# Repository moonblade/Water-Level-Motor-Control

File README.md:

# Water-Level-Motor-Control

A companion to water level indicator. Having a water level indicator is cool and all, dont get me wrong, but my lazy ass can't be bothered to get up and manually switch on the motor and switch it off when the indicator tells me to. So whats the solution? Of course, automate it.

The major issue preventing me from doing this along with the indicator was that the motor switch was an outdoor style, push on push off switch and it was a bit daunting to mess around with it and add my own relay circuits to it. So I had kept it aside for a while.

### Raspberry pi controller

In the meantime, I bought a raspberry pi, and wasn't really doing much on it, so thinking I should at least be using it for something, ended up setting up grafana, and prometheus on it to visualize the water levels in sweet graphs.

Then figured would mess around with it a tiny bit more, and ended up writing an overcomplicated piece of code that checks the measurements from the last 3 minutes from prometheus, averages it, and then displays that as the percentage. There was an intermittent issue that sometimes wrong readings would come up in the sensor on the motor, so wrote a filter that removes any reading that is greater than 2 standard deviations away from mean for the last 3 minutes, and then the average is taken. 

This worked well for a while, but prometheus was giving all sorts of errors. Couldn't be bothered to deal with them in the long run when changing timezone and the size gap were the solutions I had to content with, so scratched it all out and ended up just using a circular array to store the previous values and then doing the calculations on it instead. It works well. At presnt prometheus service is failing and need to debug why, but the graphs can wait for now

### Automatic controller

Figured I'd at least making some in roads on how to tackle this, so got a wemos d1 chip, and a four channel relay, and whipped up a quick prototype that could take instructions from firebase. Intentionally made it stupid and controlled by the rpi so that modifications can be made on the fly by changing rpi code without having to touch the chip. Anyway, it takes on or off command from the rtdb and if its internal state was different from the command given, it would turn on or off the motor as needed. There were some issues with me not understanding the wiring of the box, namely that the offswitch was a normally closed connection and the switch breaks the connection and not the other way around, so after a bit of headscratching ended up wiring that in series with the existing connection so that both the manual and the auto switch would work. Didn't want the hassle of a phone charger for power like last time, so wired up an ac to dc convertor within the circuit itself so that it could be powered with the current to motor itself.

connections

assembled into its box

Wiring into the switch

Final state

Added the corresponding code in raspberry pi code to turn it on and off when critical thresholds were reached and added a ui for user to control the settings and turn motor on and off manually and also to turn off automatic water control. Gave it a go and wonder of wonders, it worked.........for a day. 

Waking up the next day I see that it should have turned the motor on, but didnt'. It had broken the very next day, post mortem analysis showed that the relay rated for 10 A had pulled close to 15 A through it and thus had died on me. So chalked that upto a learning experience and figured the next version would need 30A relays.

### Auto controller v2

5V 30A relays are kinda hard to find, especially if you want them as multiple channel modules, you'd need to import them from US as they seem to be the only ones making it. So ordered a couple of relays, opted for single ones since the other ones would take too long, and started work on the next board.

Throughout this project I'd done pcb designs on eagle, and later [on easyEDA](https://easyeda.com/editor#id=b41bb882b032482bb2b21c925477a603) but whenever I try to get them printed (on normal paper as a test run), I'd find that it was too small, I dont know if its a library fault or the component I chose was wrong or some other printer settings. Even ignoring the pcb printing, when I tried to make holes on a copper clad to practice with a hand drill, the resulting "line" of holes was more like a curve and I'd have trouble fitting in anything close to an IC chip in it. So figured I still needed training before I could use custom pcbs, or better yet it would make sense to just print it commercially than go through this again.

Anyway for the second round, added a second ac to dc convertor so that I could determine the current state of the motor from external signals instead of relying on an internal toggle, this way I could turn off the motor even if it was turned on by hand. I had bought two relays figuring I could turn the two on switches with one and the off switch with the other, so when I got the board ready and wired it up that way, what ended up happening is that the motor could not be turned off. If you turn it off, it just turned back on again. Facepalm moment, thinking of connecting two different circuits in one relay.

Lesson learnt, ordered the next relay and waited for it. After it arrived, added that in and tested it. But it didn't seem to work properly, it worked in brief tests, ie it could turn off the motor when it was on, but nothing else. Wierd. So I took off the chip and tried to flash new code to it, only to realize the chip was not functioning anymore. So I ordered a couple of new chips and waited for it to arrive.

Meanwhile, the water level sensor up top decided it wanted to go for a swim and took a dive into the water tank killing itself. So ended up spending time creating a v2 for the sensor as well. Which was a whole another ordeal.

The fault implied a wrong connection somewhere in the board. Since this was already wired into the switch board, it was a pain in the ass to test each conenction. Finally figuring out that the board was fine, but I'd connected the two ac to dc convertors in reverse, the sensing one and the power one were interchanged. So connected it properly. And plugged in the new chips. The chips were working properly and doing their job but the raspberry pi code that I'd updated in the meantime was now broken, and the correct commands were not being sent to turn the motor on and off. Sigh. This is integration hell.

After two days of hard debugging, finally figured out the issue. It wasn't working ....wait for it..... because it was turned off in the settings. Sigh. Turned it on and it started working without a hitch.

new circuit

finished product in a shinier box

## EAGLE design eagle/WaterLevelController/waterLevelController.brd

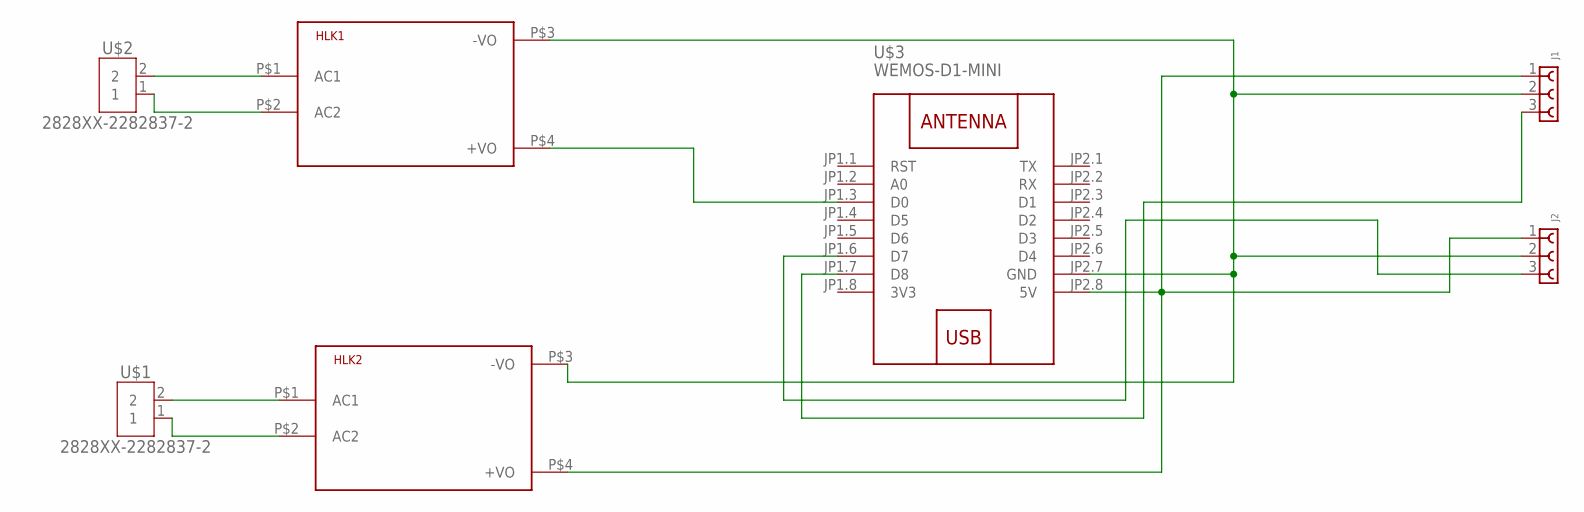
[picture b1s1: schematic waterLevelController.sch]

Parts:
HLK1, HLK2: HLK-PM013W; HLK-PM01
J1, J2: 6130XX11821_61300311821; 61300311821
U$1, U$2: 2828XX-2282837-2; TERMBLK_508-2N
U$3: WEMOS-D1-MINI

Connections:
3V3: U$3.JP1.8 (3V3)
unnamed: HLK1.P$2 (AC2), U$2.1
unnamed: HLK2.P$4 (+VO), J1.1, J2.1, U$3.JP2.8 (5V)
unnamed: HLK1.P$1 (AC1), U$2.2
unnamed: HLK1.P$3 (-VO), HLK2.P$3 (-VO), J1.2, J2.2, U$3.JP2.7 (GND)
unnamed: HLK2.P$2 (AC2), U$1.1
unnamed: HLK2.P$1 (AC1), U$1.2
unnamed: HLK1.P$4 (+VO), U$3.JP1.3 (D0)
unnamed: J1.3, U$3.JP1.7 (D8)
unnamed: J2.3, U$3.JP1.6 (D7)

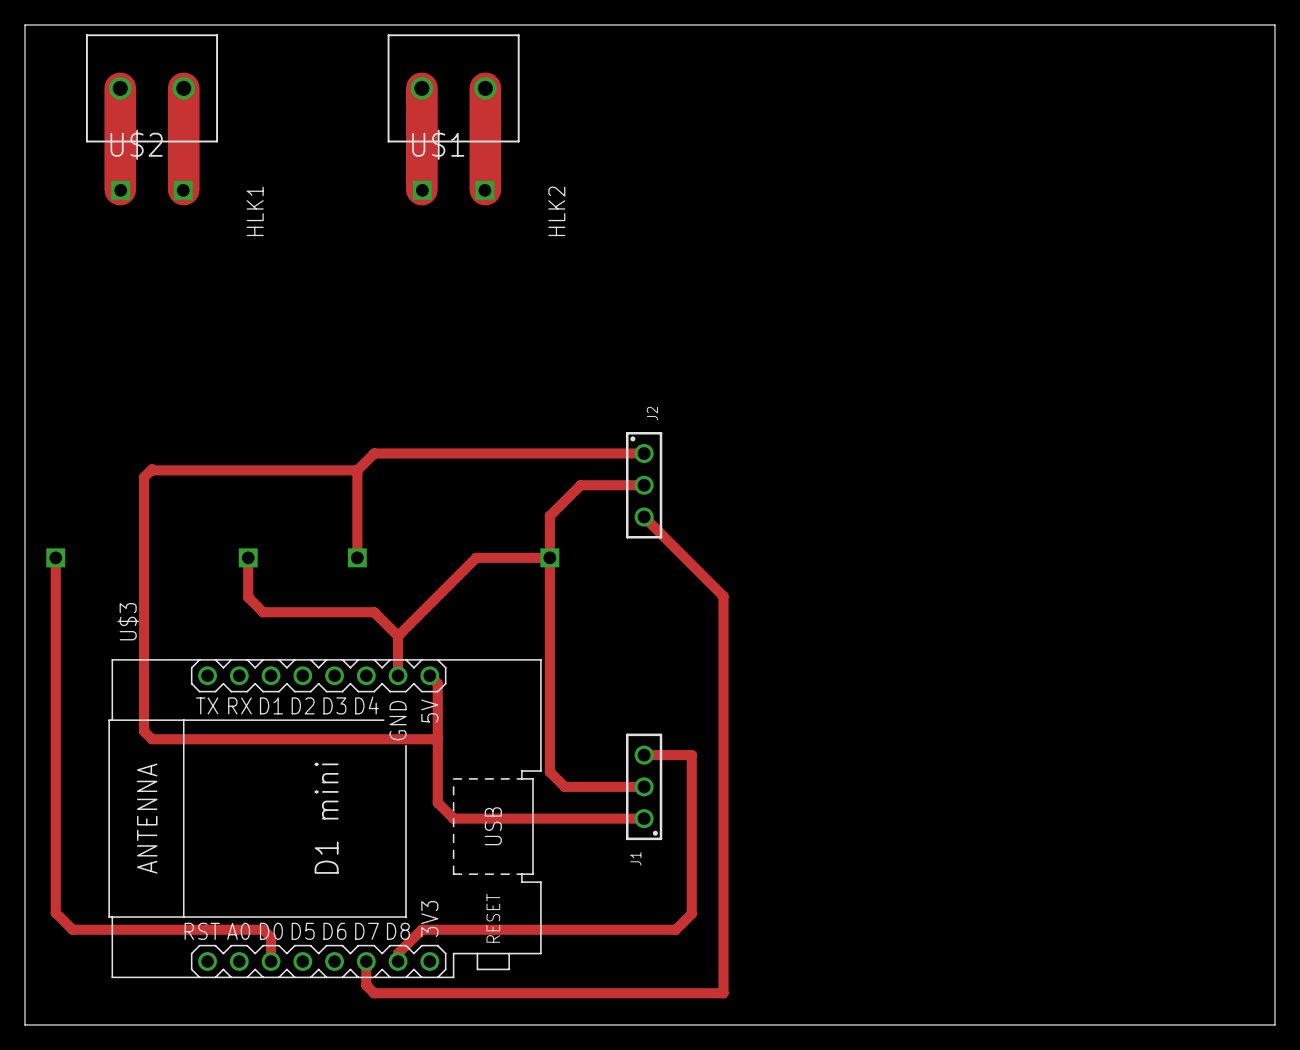
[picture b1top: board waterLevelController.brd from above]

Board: 2 copper layers, 100.0 x 80.0 mm, 7 parts (0 on the bottom side), 9 nets.

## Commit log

2021-07-13 Get data from firebase db
2021-07-13 Move to js instead
2021-07-13 add npm start
2021-07-14 Add raw data gauge
2021-07-16 Current changes
2021-07-16 Add logger and motor controller v1
2021-07-16 Use online settings
2021-07-16 Cleanup output
2021-07-18 Add motor controller naive code
2021-07-18 typo
2021-07-19 Add rolling percentage value into graph
2021-07-19 Remove logs
2021-07-24 Added motorcontroller full code
2021-07-24 Add controller mappings
2021-07-24 fix link
2021-07-24 cors
2021-07-24 measurement to percentage instead
2021-07-24 Add offtimes online
2021-07-24 Add more variables
2021-07-24 Add more settings:
2021-07-24 Update url
2021-07-24 Debug statements
2021-07-25 fix issue with temporary fluctuation
2021-08-05 Debug to console.log
2021-08-09 add timestamp for percentage update
2021-08-09 Off is controlled too
2021-08-10 minor fixes
2021-08-10 typo:
2021-08-10 add five mins of empty time
2021-08-10 Raw measure
2021-08-10 Add more logs
2021-08-10 more logging
2021-08-12 remove lag
2021-08-15 add logging changes
2021-08-17 Eagle init
2021-08-17 Routed
2021-08-17 add pdf
2021-08-17 Changes to have current input from ac instead
2021-08-19 Added more code
2021-08-20 Added none state
2021-08-23 Add timeout for none
2021-08-23 Change last turn on to be based on state instead
2021-08-23 changed to last turn on variable for turn off as well
2021-08-24 Add startbeforeminutes in rtdb settings
2021-08-24 Add end time before as well
2021-09-05 remove requirement for prometheus
2021-09-05 3 minutes of data
2021-09-06 Change wifi
2021-09-06 Minor optimize
2021-09-07 Minor changes to debugging
2021-09-09 add timeout between commands
2021-09-14 Update motor controller to switch to direct mode when rpi is down
2021-09-16 Simplify motor controller code
2021-10-03 Remove motorcontroller
2021-10-11 Update with motor state as well
2021-10-11 add multiple checks before turning on
2021-10-13 updaet

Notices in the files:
parts and their libraries:
Wurth_Connectors_WR-PHD: Copyright: Würth Elektronik
diy-modules: Released under the Creative Commons Attribution 4.0 International License: http://creativecommons.org/licenses/by/4.0
